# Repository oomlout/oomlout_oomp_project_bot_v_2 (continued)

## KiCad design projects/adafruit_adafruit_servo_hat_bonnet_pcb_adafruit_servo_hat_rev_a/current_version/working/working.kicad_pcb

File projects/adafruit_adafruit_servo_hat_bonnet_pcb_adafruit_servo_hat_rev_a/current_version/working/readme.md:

# adafruit_servo_hat_bonnet_pcb
 
## summary 
* id: adafruit_adafruit_servo_hat_bonnet_pcb_adafruit_servo_hat_rev_a
* user: adafruit
* name: adafruit_servo_hat_bonnet_pcb
* board: adafruit_servo_hat_rev_a
* repo: https://github.com/adafruit/Adafruit-Servo-HAT-Bonnet-PCB

* src_file_repo_sch: 
* src_file_repo_sch_link: https://github.com/adafruit/Adafruit-Servo-HAT-Bonnet-PCB/tree/master/
* full details link: https://github.com/oomlout/oomlout_oomp_project_bot_v_2/tree/main/projects/adafruit_adafruit_servo_hat_bonnet_pcb_adafruit_servo_hat_rev_a/current_version/working  

## schematic  
  
[schematic (pdf)](working_schematic.pdf) 

## pcb  

[board (pdf)](working.pdf)  

## working_bom
| Id | Designator | Footprint | Quantity | Designation | Supplier and ref |  | None | 
| --- | --- | --- | --- | --- | --- | --- | --- | 
| 1 | R4,R5 | RESPACK_4X0603 | 2 | 10K |  |  | [''] | 
| 2 | R10 | _0805MP | 1 | 470 |  |  | [''] | 
| 3 | U2 | TSSOP28 | 1 | PCA9685 |  |  | [''] | 
| 4 | SJ1 | SOLDERJUMPER_CLOSEDWIRE | 1 | WP |  |  | [''] | 
| 5 | R11,R12,R14,R13 | RESPACK_4X0603 | 4 | 220 |  |  | [''] | 
| 6 | R1,R3,R2 | 0805-NO | 3 | 3.9K |  |  | [''] | 
| 7 | FID3,FID1,FID2 | FIDUCIAL_1MM | 3 | FIDUCIAL" |  |  | [''] | 
| 8 | SJ_A5,SJ_A1,SJ_A4,SJ_A0,SJ_A3,SJ_A2 | SOLDERJUMPER_REFLOW_NOPASTE | 6 |  |  |  | [''] | 
| 9 | LED1 | CHIPLED_0805_NOOUTLINE | 1 | GREEN |  |  | [''] | 
| 10 | U$6 | PCBFEAT-REV-056 | 1 |  |  |  | [''] | 
| 11 | UNK5VIN0 | TERMBLOCK_1X2-3.5MM | 1 | 3.5mm term |  |  | [''] | 
| 12 | R7 | 0805-NO | 1 | 10K |  |  | [''] | 
| 13 | JP5,JP6,JP2,JP1 | 3X04 | 4 |  |  |  | [''] | 
| 14 | C2 | E3,5-8 | 1 |  |  |  | [''] | 
| 15 | U1 | SOIC8_150MIL | 1 | CAT24C32 |  |  | [''] | 
| 16 | CONN1 | 1X25_ROUND_70MIL | 1 | HEADER-1X25 |  |  | [''] | 
| 17 | RPI1 | PI_HAT_SLOTS | 1 | RASPBERRYPI_BPLUS_HATSLOTS |  |  | [''] | 
| 18 | U$5 | PIHATLOGO | 1 |  |  |  | [''] | 
| 19 | Q1 | TO252 | 1 | AOD417 |  |  | [''] | 
| 20 | C1 | 0805-NO | 1 | 10uF |  |  | [''] | 
| 21 | X1 | DCJACK_2MM_SMT | 1 | 2.1mm SMT |  |  | [''] | 
| 22 | U$51 | ADAFRUIT_5MM | 1 |  |  |  | [''] | 
| 23 | TP6,TP1,TP3,TP4,TP5,TP2 | B1,27 | 6 | TPB1,27 |  |  | [''] | 

## bom_schematic
no data

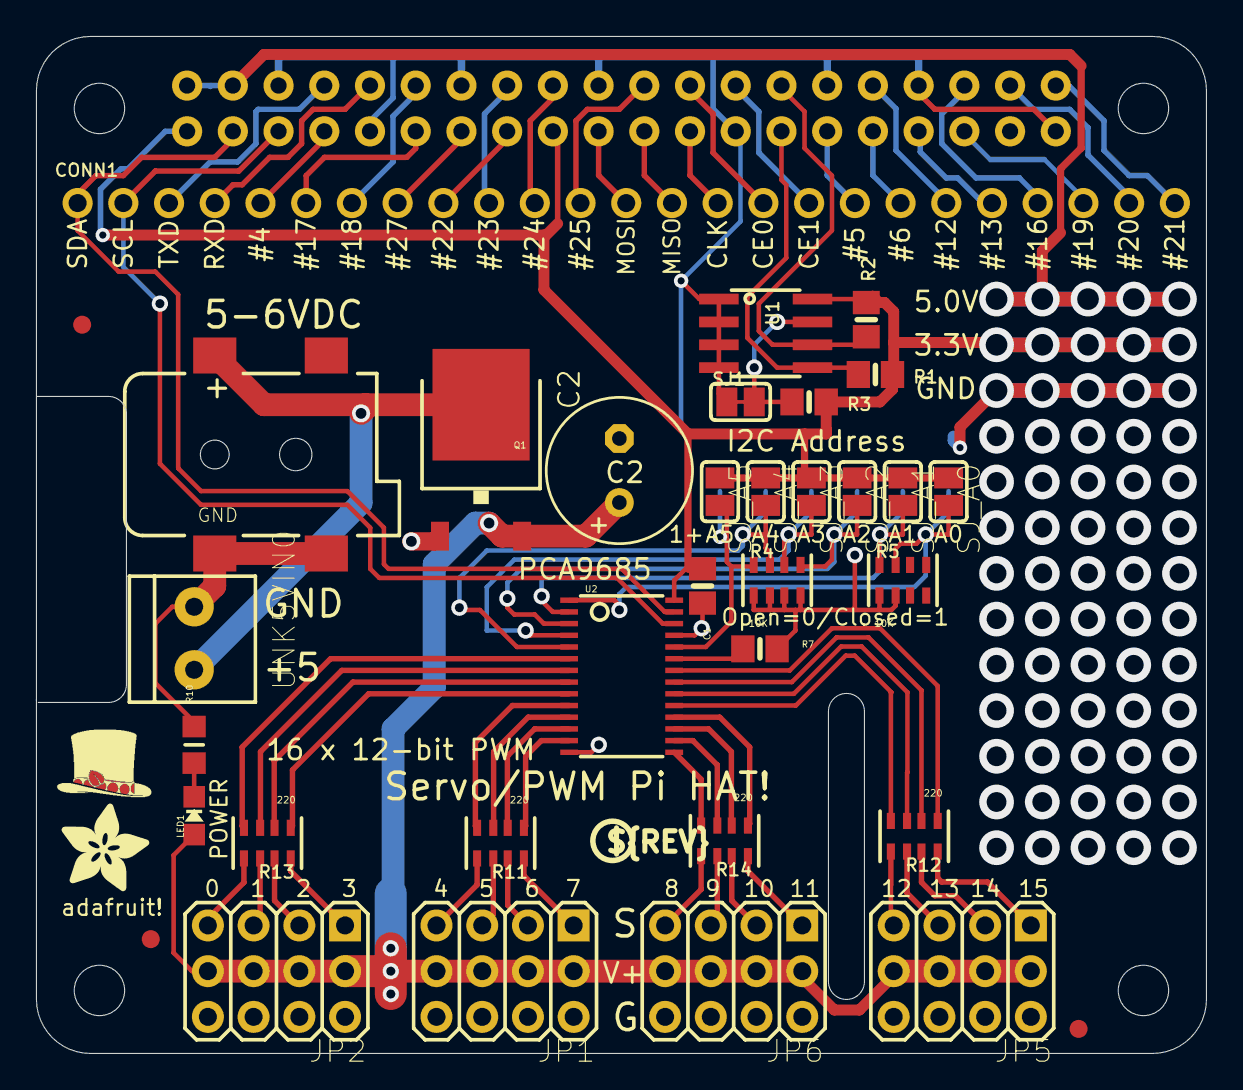
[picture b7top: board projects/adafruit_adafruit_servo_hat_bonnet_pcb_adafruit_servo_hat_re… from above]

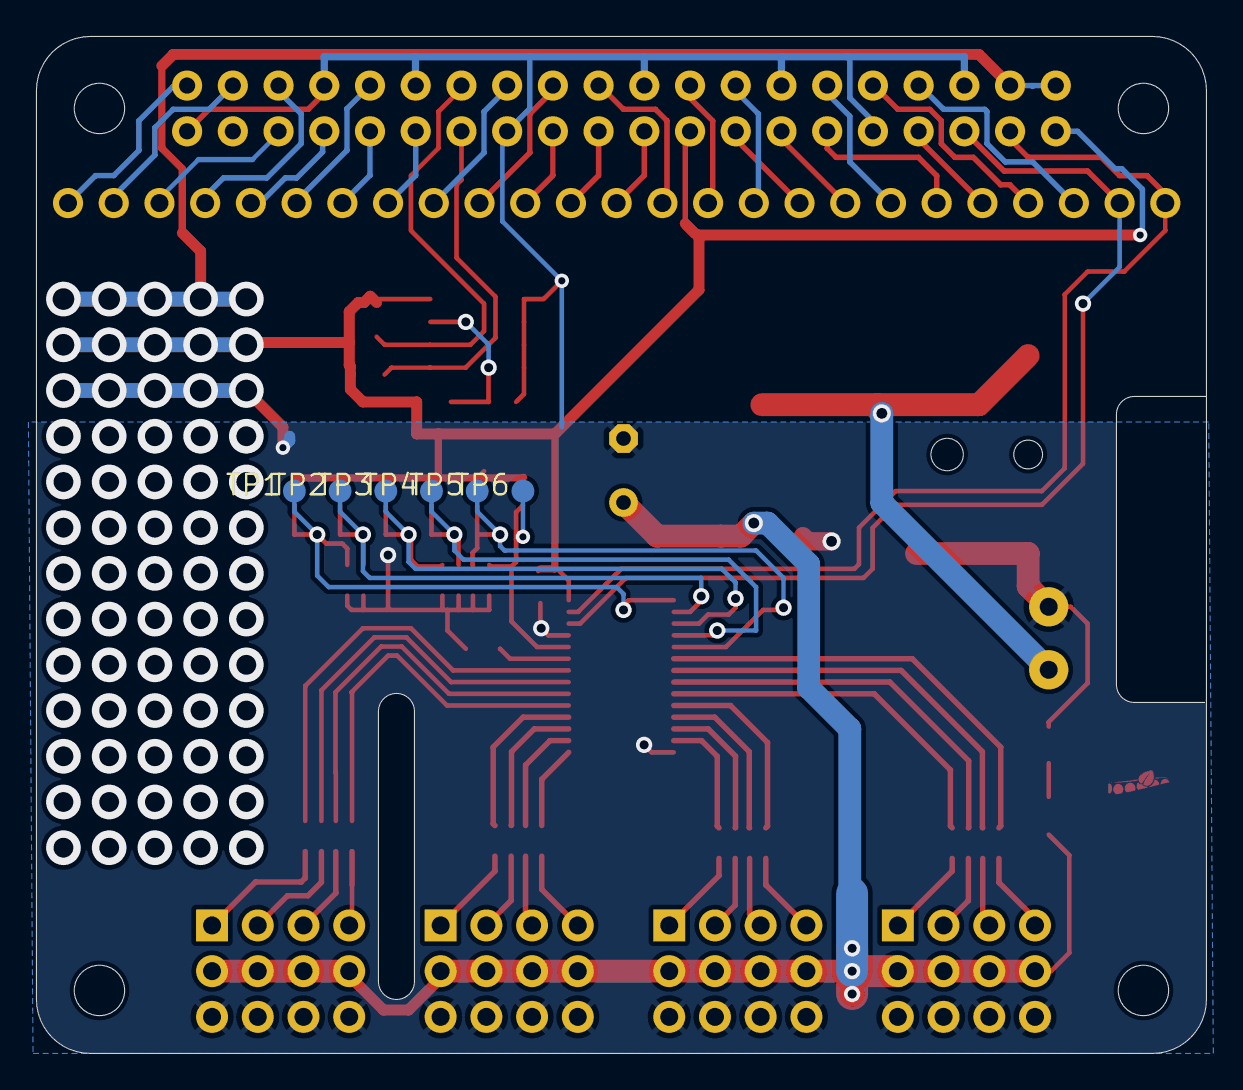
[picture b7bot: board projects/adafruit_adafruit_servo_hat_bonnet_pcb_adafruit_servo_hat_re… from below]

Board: 2 copper layers, 65.0 x 56.5 mm, 44 parts (6 on the bottom side), 73 nets.

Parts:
C1: 10uF; 0805-NO
C2: E3,5-8
CONN1: HEADER-1X25; 1X25_ROUND_70MIL
FID1, FID2, FID3: FIDUCIAL""; FIDUCIAL_1MM
JP1, JP2, JP5, JP6: 3X04
LED1: GREEN; CHIPLED_0805_NOOUTLINE
Q1: AOD417; TO252
R1, R2, R3: 3.9K; 0805-NO
R4, R5: 10K; RESPACK_4X0603
R7: 10K; 0805-NO
R10: 470; _0805MP
R11, R12, R13, R14: 220; RESPACK_4X0603
RPI1: RASPBERRYPI_BPLUS_HATSLOTS; PI_HAT_SLOTS
SJ1: WP; SOLDERJUMPER_CLOSEDWIRE
SJ_A0, SJ_A1, SJ_A2, SJ_A3, SJ_A4, SJ_A5: SOLDERJUMPER_REFLOW_NOPASTE
TP1, TP2, TP3, TP4, TP5, TP6: TPB1,27; B1,27
U1: CAT24C32; SOIC8_150MIL
U2: PCA9685; TSSOP28
U$5: PIHATLOGO
U$6: PCBFEAT-REV-056
U$51: ADAFRUIT_5MM
UNK5VIN0: 3.5mm term; TERMBLOCK_1X2-3.5MM
X1: 2.1mm SMT; DCJACK_2MM_SMT

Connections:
3.3V: C1.1, R1.2, R2.2, R3.2, RPI1.1, RPI1.17, SJ_A0.1, SJ_A1.1, SJ_A2.1, SJ_A3.1, SJ_A4.1, SJ_A5.1, U1.8, U2.28
5.0V: RPI1.2, RPI1.4
+5V: C2.+, JP1.2, JP1.5, JP1.8, JP1.11, JP2.2, JP2.5, JP2.8, JP2.11, JP5.2, JP5.5, JP5.8, JP5.11, JP6.2, JP6.5, JP6.8, JP6.11, LED1.A, Q1.2
A0: R5.7, SJ_A0.2, TP1.TP, U2.1
A1: R5.8, SJ_A1.2, TP2.TP, U2.2
A2: R4.5, SJ_A2.2, TP3.TP, U2.3
A3: R4.6, SJ_A3.2, TP4.TP, U2.4
A4: R4.7, SJ_A4.2, TP5.TP, U2.5
A5: R4.8, SJ_A5.2, TP6.TP, U2.24
EECLK: R2.1, RPI1.28, U1.6
EEDATA: R1.1, RPI1.27, U1.5
GND: C1.2, C2.-, JP1.3, JP1.6, JP1.9, JP1.12, JP2.3, JP2.6, JP2.9, JP2.12, JP5.3, JP5.6, JP5.9, JP5.12, JP6.3, JP6.6, JP6.9, JP6.12, Q1.1, R4.1, R4.2, R4.3, R4.4, R5.1, R5.2, R7.2, R10.2, RPI1.6, RPI1.9, RPI1.14, RPI1.20, RPI1.25, RPI1.30, RPI1.34, RPI1.39, SJ1.1, U1.1, U1.2, U1.3, U1.4, U2.14, U2.25, UNK5VIN0.2, X1.GND, X1.GNDBREAK
GPIO4: CONN1.5, RPI1.7
GPIO5: CONN1.18, RPI1.29
GPIO6: CONN1.19, RPI1.31
GPIO12: CONN1.20, RPI1.32
GPIO13: CONN1.21, RPI1.33
GPIO16: CONN1.22, RPI1.36
GPIO17: CONN1.6, RPI1.11
GPIO18: CONN1.7, RPI1.12
GPIO19: CONN1.23, RPI1.35
GPIO20: CONN1.24, RPI1.38
GPIO21: CONN1.25, RPI1.40
GPIO22: CONN1.9, RPI1.15
GPIO23: CONN1.10, RPI1.16
GPIO24: CONN1.11, RPI1.18
GPIO25: CONN1.12, RPI1.22
GPIO27: CONN1.8, RPI1.13
unnamed: R3.1, SJ1.2, U1.7
unnamed: LED1.C, R10.1
unnamed: JP1.4, R11.7
unnamed: JP1.1, R11.8
unnamed: JP1.7, R11.6
unnamed: JP1.10, R11.5
unnamed: JP2.1, R13.8
unnamed: JP2.4, R13.7
unnamed: JP2.7, R13.6
unnamed: JP2.10, R13.5
unnamed: JP6.10, R14.5
unnamed: JP6.7, R14.6
unnamed: JP6.4, R14.7
unnamed: JP6.1, R14.8
unnamed: JP5.10, R12.5
unnamed: JP5.7, R12.6
unnamed: JP5.4, R12.7
unnamed: JP5.1, R12.8
OE: R7.1, U2.23
PWM0: R13.4, U2.6
PWM1: R13.3, U2.7
PWM2: R13.2, U2.8
PWM3: R13.1, U2.9
PWM4: R11.4, U2.10
PWM5: R11.3, U2.11
PWM6: R11.2, U2.12
PWM7: R11.1, U2.13
PWM8: R14.4, U2.15
PWM9: R14.3, U2.16
PWM10: R14.2, U2.17
PWM11: R14.1, U2.18
PWM12: R12.4, U2.19
PWM13: R12.3, U2.20
PWM14: R12.2, U2.21
PWM15: R12.1, U2.22
PWRIN: Q1.3, UNK5VIN0.1, X1.PWR
RXD: CONN1.4, RPI1.10
SCL: CONN1.2, RPI1.5, U2.26
SDA: CONN1.1, RPI1.3, U2.27
SPI_CE0: CONN1.16, RPI1.24
SPI_CE1: CONN1.17, RPI1.26
SPI_MISO: CONN1.14, RPI1.21
SPI_MOSI: CONN1.13, RPI1.19
SPI_SCLK: CONN1.15, RPI1.23
TXD: CONN1.3, RPI1.8
